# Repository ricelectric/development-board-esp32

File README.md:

# development-board-esp32

This is an open source repository for a development board featuring ESP32-C3, perfect for IoT projects. More information is available [here](https://qiita.com/ricelectric/items/990088bb8d065cbd0641).

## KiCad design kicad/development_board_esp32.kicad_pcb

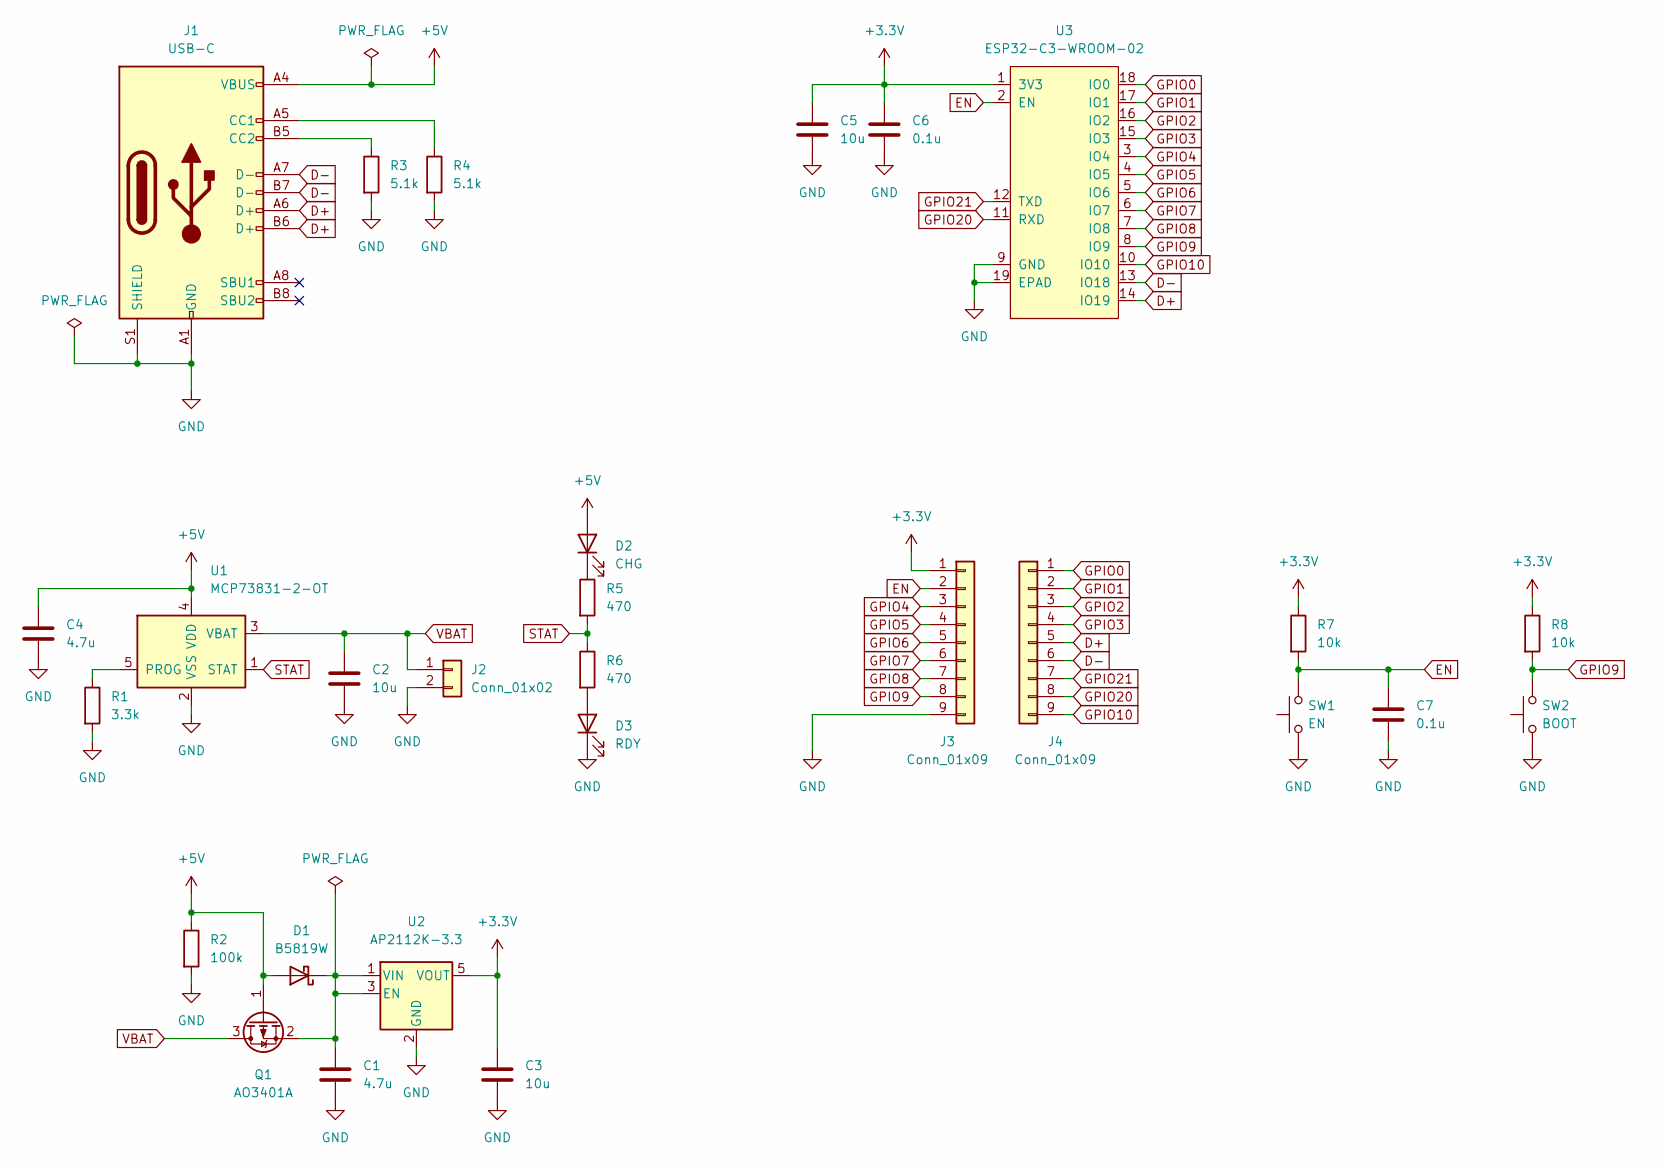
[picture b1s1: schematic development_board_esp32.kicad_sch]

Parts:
C1, C4: 4.7u; C_0402_1005Metric
C2, C3, C5: 10u; C_0402_1005Metric
C6, C7: 0.1u; C_0402_1005Metric
D1: B5819W; D_SOD-123
D2: CHG; LED_0603_1608Metric
D3: RDY; LED_0603_1608Metric
J1: USB-C; USB_C_Receptacle_XKB_U262-16XN-4BVC11
J2: Conn_01x02; JST_PH_B2B-PH-K_1x02_P2.00mm_Vertical
J3, J4: Conn_01x09; PinHeader_1x09_P2.54mm_Vertical
Q1: AO3401A; SOT-23
R1: 3.3k; R_0402_1005Metric
R2: 100k; R_0402_1005Metric
R3, R4: 5.1k; R_0402_1005Metric
R5, R6: 470; R_0402_1005Metric
R7, R8: 10k; R_0402_1005Metric
SW1: EN; SW_Push_SPST_NO_Alps_SKRK
SW2: BOOT; SW_Push_SPST_NO_Alps_SKRK
U1: MCP73831-2-OT; SOT-23-5
U2: AP2112K-3.3; SOT-23-5
U3: ESP32-C3-WROOM-02

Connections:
+3.3V: C3.1, C5.1, C6.1, J3.1, R7.1, R8.1, U2.5 (VOUT), U3.1 (3V3)
+5V: C4.1, D1.2 (A), D2.2 (A), J1.A4 (VBUS), J1.A9 (VBUS), J1.B4 (VBUS), J1.B9 (VBUS), Q1.1 (G), R2.1, U1.4 (VDD)
D+: J1.A6 (D+), J1.B6 (D+), J4.5, U3.14 (IO19)
D-: J1.A7 (D-), J1.B7 (D-), J4.6, U3.13 (IO18)
EN: C7.1, J3.2, R7.2, SW1.2, U3.2 (EN)
GND: C1.2, C2.2, C3.2, C4.2, C5.2, C6.2, C7.2, D3.1 (K), J1.A1 (GND), J1.A12 (GND), J1.B1 (GND), J1.B12 (GND), J1.S1 (SHIELD), J2.2, J3.9, R1.2, R2.2, R3.2, R4.2, SW1.1, SW2.1, U1.2 (VSS), U2.2 (GND), U3.9 (GND), U3.19 (EPAD)
GPIO0: J4.1, U3.18 (IO0)
GPIO1: J4.2, U3.17 (IO1)
GPIO2: J4.3, U3.16 (IO2)
GPIO3: J4.4, U3.15 (IO3)
GPIO4: J3.3, U3.3 (IO4)
GPIO5: J3.4, U3.4 (IO5)
GPIO6: J3.5, U3.5 (IO6)
GPIO7: J3.6, U3.6 (IO7)
GPIO8: J3.7, U3.7 (IO8)
GPIO9: J3.8, R8.2, SW2.2, U3.8 (IO9)
GPIO10: J4.9, U3.10 (IO10)
GPIO20: J4.8, U3.11 (RXD)
GPIO21: J4.7, U3.12 (TXD)
unnamed: C1.1, D1.1 (K), Q1.2 (S), U2.1 (VIN), U2.3 (EN)
unnamed: D2.1 (K), R5.1
unnamed: D3.2 (A), R6.2
unnamed: J1.A5 (CC1), R4.1
unnamed: J1.B5 (CC2), R3.1
unnamed: R1.1, U1.5 (PROG)
STAT: R5.2, R6.1, U1.1 (STAT)
VBAT: C2.1, J2.1, Q1.3 (D), U1.3 (VBAT)

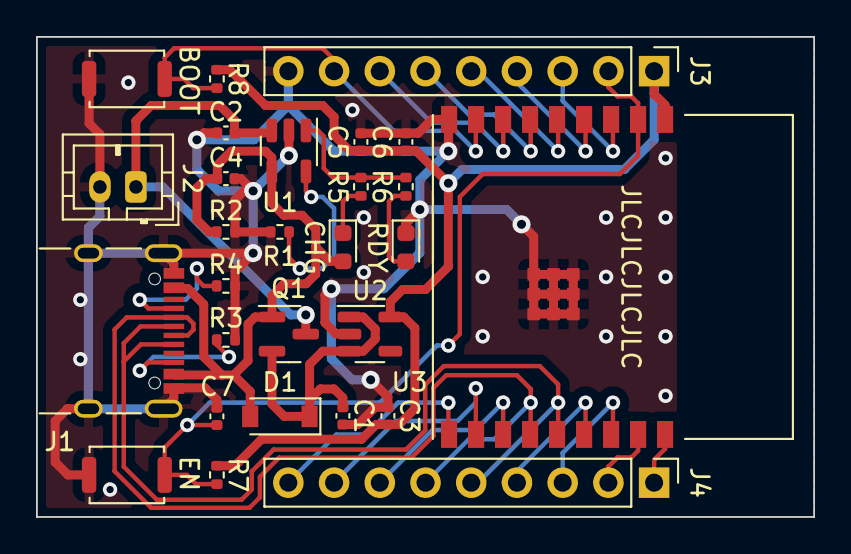
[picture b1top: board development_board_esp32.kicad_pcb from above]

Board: 2 copper layers, 43.2 x 26.7 mm, 28 parts (0 on the bottom side), 27 nets.

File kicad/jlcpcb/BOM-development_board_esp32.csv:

Comment,Designator,Footprint,LCSC
EN,"SW1,SW2",SW_Push_SPST_NO_Alps_SKRK,C115357
AO3401A,Q1,SOT-23,C15127
10u,"C2,C3,C5",C_0402_1005Metric,C15525
CHG,"D2,D3",LED_0603_1608Metric,C2286
4.7u,"C1,C4",C_0402_1005Metric,C23733
470,"R5,R6",R_0402_1005Metric,C25117
100k,R2,R_0402_1005Metric,C25741
10k,"R7,R8",R_0402_1005Metric,C25744
3.3k,R1,R_0402_1005Metric,C25890
5.1k,"R3,R4",R_0402_1005Metric,C25905
0.1u,"C6,C7",C_0402_1005Metric,C307331
USB-C,J1,USB_C_Receptacle_XKB_U262-16XN-4BVC11,C319148
MCP73831-2-OT,U1,SOT-23-5,C424093
AP2112K-3.3,U2,SOT-23-5,C51118
B5819W,D1,D_SOD-123,C8598
Conn_01x09,J4,PinHeader_1x09_P2.54mm_Vertical,
ESP32-C3-WROOM-02,U3,ESP32-C3-WROOM-02,
Conn_01x09,J3,PinHeader_1x09_P2.54mm_Vertical,
Conn_01x02,J2,JST_PH_B2B-PH-K_1x02_P2.00mm_Vertical,
